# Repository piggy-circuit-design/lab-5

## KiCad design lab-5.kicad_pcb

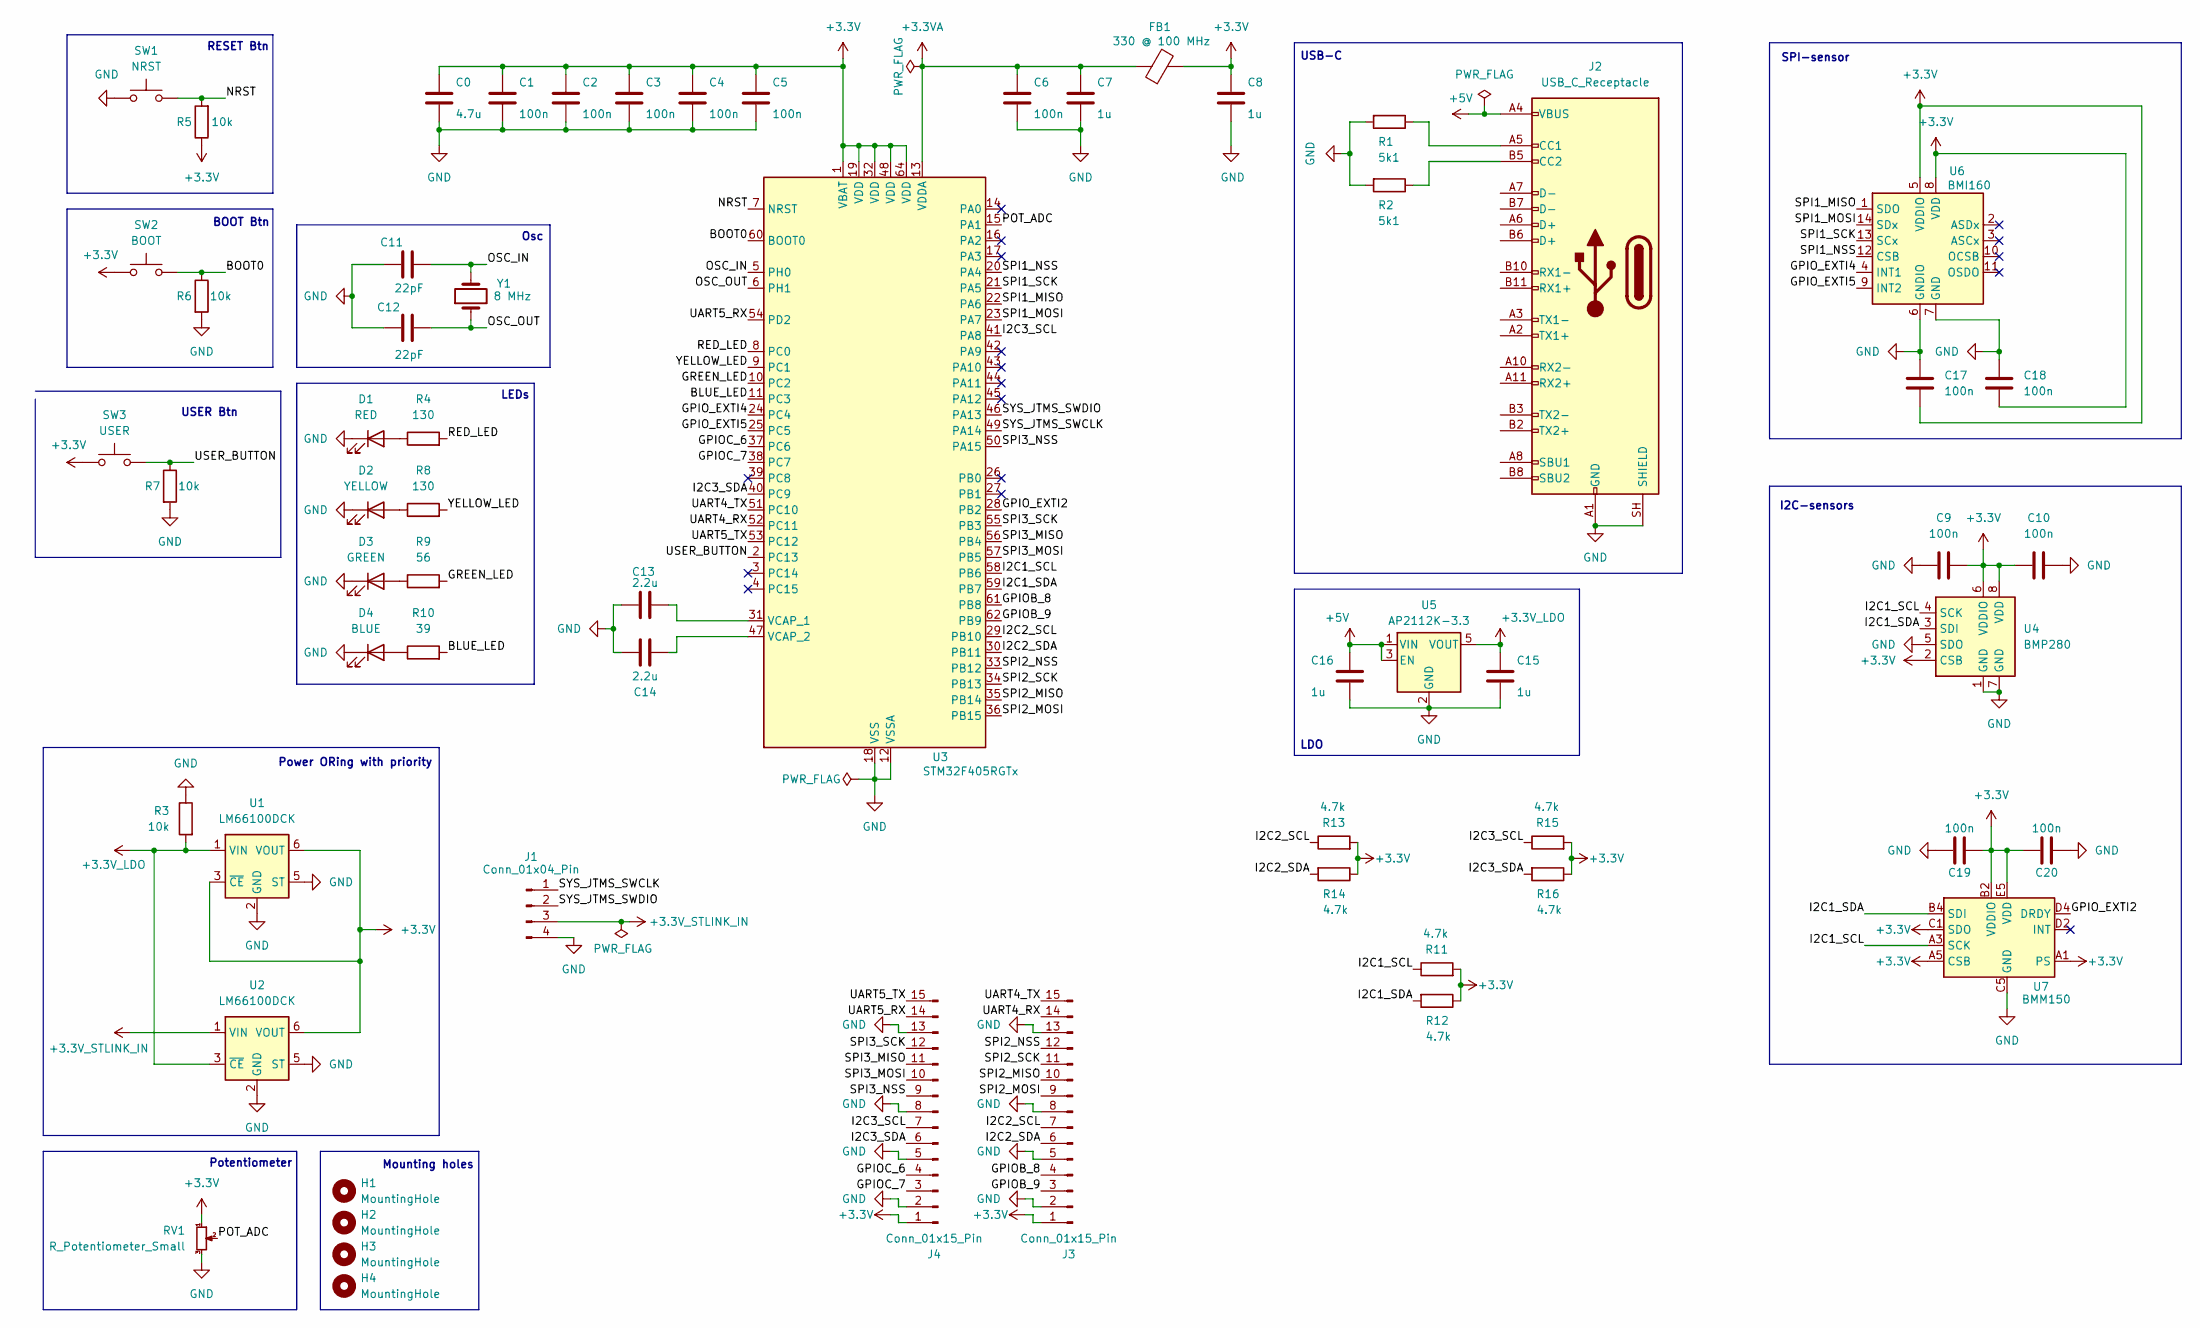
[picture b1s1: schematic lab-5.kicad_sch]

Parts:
C0: 4.7u; C_0603_1608Metric
C1, C2, C3, C4, C5, C6, C9, C10, C17, C18, C19, C20: 100n; C_0402_1005Metric
C7, C8, C15, C16: 1u; C_0603_1608Metric
C11, C12: 22pF; C_0402_1005Metric
C13, C14: 2.2u; C_0402_1005Metric
D1: RED; LED_0805_2012Metric
D2: YELLOW; LED_0805_2012Metric
D3: GREEN; LED_0805_2012Metric
D4: BLUE; LED_0805_2012Metric
FB1: 330 @ 100 MHz; L_0603_1608Metric
H1, H2, H3, H4: MountingHole; MountingHole_2.2mm_M2_Pad
J1: Conn_01x04_Pin; PinHeader_1x04_P2.54mm_Vertical
J2: USB_C_Receptacle; USB_C_Receptacle_Amphenol_12401610E4-2A
J3, J4: Conn_01x15_Pin; PinHeader_1x15_P2.54mm_Vertical
R1, R2: 5k1; R_0603_1608Metric
R3, R5, R6, R7: 10k; R_0402_1005Metric
R4, R8: 130; R_0402_1005Metric
R9: 56; R_0402_1005Metric
R10: 39; R_0402_1005Metric
R11, R12, R13, R14, R15, R16: 4.7k; R_0402_1005Metric
RV1: R_Potentiometer_Small; Potentiometer_Bourns_3224G_Horizontal
SW1: NRST; SW_SPST_PTS647_Sx38
SW2: BOOT; SW_SPST_PTS647_Sx38
SW3: USER; SW_SPST_PTS647_Sx38
U1, U2: LM66100DCK; SOT-363_SC-70-6
U3: STM32F405RGTx; LQFP-64_10x10mm_P0.5mm
U4: BMP280; Bosch_LGA-8_2x2.5mm_P0.65mm_ClockwisePinNumbering
U5: AP2112K-3.3; SOT-23-5
U6: BMI160; Bosch_LGA-14_3x2.5mm_P0.5mm
U7: BMM150; WLCSP-12_1.56x1.56mm_P0.4mm
Y1: 8 MHz; Crystal_SMD_2520-4Pin_2.5x2.0mm

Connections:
+3.3V: C0.1, C1.1, C2.1, C3.1, C4.1, C5.1, C8.1, C9.2, C10.1, C17.1, C18.1, C19.2, C20.1, FB1.2, J3.1, J4.1, R5.1, R11.2, R12.1, R13.2, R14.1, R15.2, R16.1, RV1.1, SW2.2, SW3.2, U1.3 (~CE), U1.6 (VOUT), U2.6 (VOUT), U3.1 (VBAT), U3.19 (VDD), U3.32 (VDD), U3.48 (VDD), U3.64 (VDD), U4.2 (CSB), U4.6 (VDDIO), U4.8 (VDD), U6.5 (VDDIO), U6.8 (VDD), U7.A1 (PS), U7.A5 (CSB), U7.B2 (VDDIO), U7.C1 (SDO), U7.E5 (VDD)
+3.3VA: C6.1, C7.1, FB1.1, U3.13 (VDDA)
+3.3V_LDO: C15.1, R3.2, U1.1 (VIN), U2.3 (~CE), U5.5 (VOUT)
+3.3V_STLINK_IN: J1.3, U2.1 (VIN)
+5V: C16.2, J2.A4 (VBUS), J2.A9 (VBUS), J2.B4 (VBUS), J2.B9 (VBUS), U5.1 (VIN), U5.3 (EN)
/BLUE_LED: R10.2, U3.11 (PC3)
/BOOT0: R6.1, SW2.1, U3.60 (BOOT0)
/GPIOB_8: J3.4, U3.61 (PB8)
/GPIOB_9: J3.3, U3.62 (PB9)
/GPIOC_6: J4.4, U3.37 (PC6)
/GPIOC_7: J4.3, U3.38 (PC7)
/GPIO_EXTI2: U3.28 (PB2), U7.D4 (DRDY)
/GPIO_EXTI4: U3.24 (PC4), U6.4 (INT1)
/GPIO_EXTI5: U3.25 (PC5), U6.9 (INT2)
/GREEN_LED: R9.2, U3.10 (PC2)
/I2C1_SCL: R11.1, U3.58 (PB6), U4.4 (SCK), U7.A3 (SCK)
/I2C1_SDA: R12.2, U3.59 (PB7), U4.3 (SDI), U7.B4 (SDI)
/I2C2_SCL: J3.7, R13.1, U3.29 (PB10)
/I2C2_SDA: J3.6, R14.2, U3.30 (PB11)
/I2C3_SCL: J4.7, R15.1, U3.41 (PA8)
/I2C3_SDA: J4.6, R16.2, U3.40 (PC9)
/NRST: R5.2, SW1.1, U3.7 (NRST)
/OSC_IN: C11.2, U3.5 (PH0), Y1.2
/OSC_OUT: C12.2, U3.6 (PH1), Y1.1
/POT_ADC: RV1.2, U3.15 (PA1)
/RED_LED: R4.2, U3.8 (PC0)
/SPI1_MISO: U3.22 (PA6), U6.1 (SDO)
/SPI1_MOSI: U3.23 (PA7), U6.14 (SDx)
/SPI1_NSS: U3.20 (PA4), U6.12 (CSB)
/SPI1_SCK: U3.21 (PA5), U6.13 (SCx)
/SPI2_MISO: J3.10, U3.35 (PB14)
/SPI2_MOSI: J3.9, U3.36 (PB15)
/SPI2_NSS: J3.12, U3.33 (PB12)
/SPI2_SCK: J3.11, U3.34 (PB13)
/SPI3_MISO: J4.11, U3.56 (PB4)
/SPI3_MOSI: J4.10, U3.57 (PB5)
/SPI3_NSS: J4.9, U3.50 (PA15)
/SPI3_SCK: J4.12, U3.55 (PB3)
/SYS_JTMS_SWCLK: J1.1, U3.49 (PA14)
/SYS_JTMS_SWDIO: J1.2, U3.46 (PA13)
/UART4_RX: J3.14, U3.52 (PC11)
/UART4_TX: J3.15, U3.51 (PC10)
/UART5_RX: J4.14, U3.54 (PD2)
/UART5_TX: J4.15, U3.53 (PC12)
/USER_BUTTON: R7.1, SW3.1, U3.2 (PC13)
/YELLOW_LED: R8.2, U3.9 (PC1)
GND: C0.2, C1.2, C2.2, C3.2, C4.2, C5.2, C6.2, C7.2, C8.2, C9.1, C10.2, C11.1, C12.1, C13.1, C14.2, C15.2, C16.1, C17.2, C18.2, C19.1, C20.2, D1.1 (K), D2.1 (K), D3.1 (K), D4.1 (K), J1.4, J2.A1 (GND), J2.A12 (GND), J2.B1 (GND), J2.B12 (GND), J2.SH (SHIELD), J3.2, J3.5, J3.8, J3.13, J4.2, J4.5, J4.8, J4.13, R1.2, R2.2, R3.1, R6.2, R7.2, RV1.3, SW1.2, U1.2 (GND), U1.5 (ST), U2.2 (GND), U2.5 (ST), U3.12 (VSSA), U3.18 (VSS), U3.63 (VSS), U4.1 (GND), U4.5 (SDO), U4.7 (GND), U5.2 (GND), U6.6 (GNDIO), U6.7 (GND), U7.C5 (GND), U7.E1 (GND), U7.E3 (GND)
unnamed: D1.2 (A), R4.1
unnamed: D2.2 (A), R8.1
unnamed: D3.2 (A), R9.1
unnamed: D4.2 (A), R10.1
unnamed: J2.A5 (CC1), R1.1
unnamed: J2.B5 (CC2), R2.1
unnamed: C13.2, U3.31 (VCAP_1)
unnamed: C14.1, U3.47 (VCAP_2)

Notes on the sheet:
LEDs
SPI-sensor
BOOT Btn
I2C-sensors
Osc
USB-C
Power ORing with priority
LDO
Mounting holes
Potentiometer
RESET Btn
USER Btn

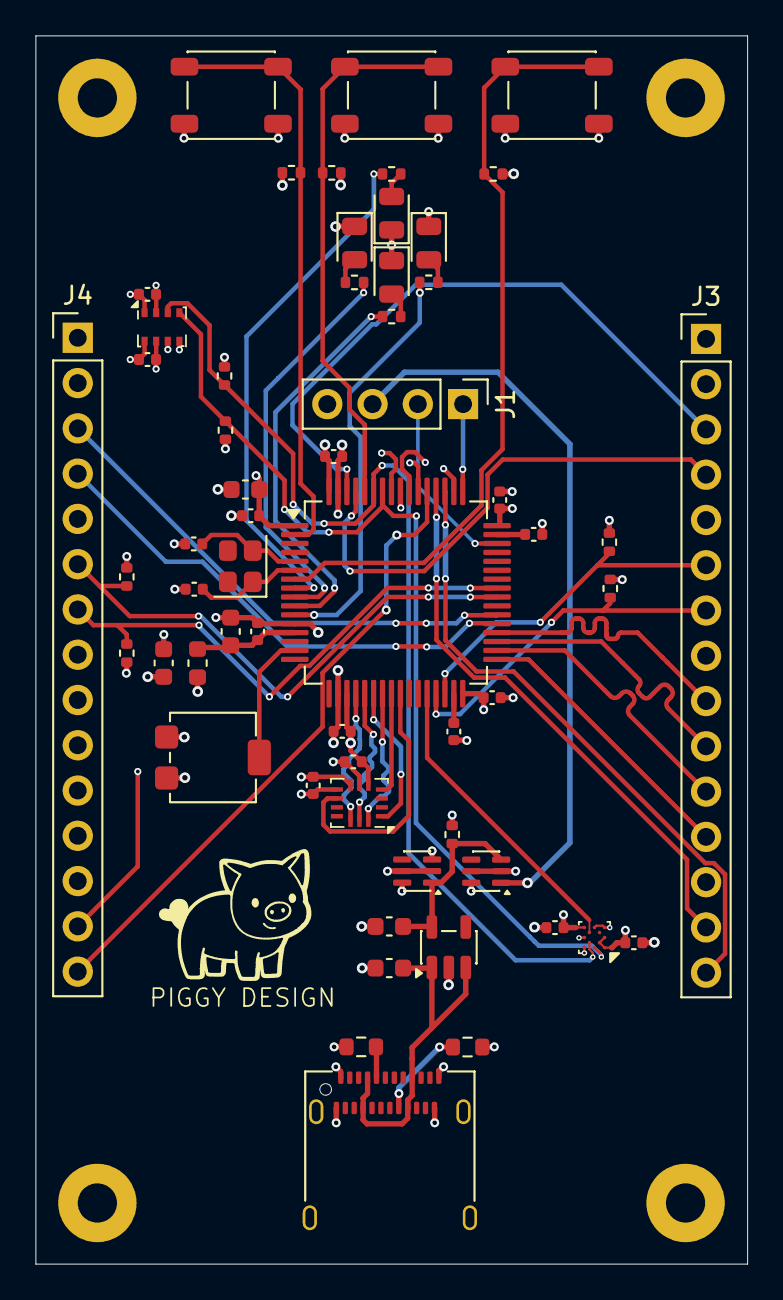
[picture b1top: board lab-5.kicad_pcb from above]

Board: 4 copper layers, 39.9 x 68.9 mm, 62 parts (0 on the bottom side), 55 nets.

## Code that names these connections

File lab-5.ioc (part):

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Mcu.Name=STM32F405RGTx
Mcu.Package=LQFP64
Mcu.UserName=STM32F405RGTx
PA1.GPIOParameters=GPIO_Label
PA1.GPIO_Label=POT_ADC
PA1.Signal=ADCx_IN1
PA13.Mode=Serial_Wire
PA13.Signal=SYS_JTMS-SWDIO
PA14.Mode=Serial_Wire
PA14.Signal=SYS_JTCK-SWCLK
PA15.Mode=NSS_Signal_Hard_Output
PA15.Signal=SPI3_NSS
PA4.Mode=NSS_Signal_Hard_Output
PA4.Signal=SPI1_NSS
PA5.Mode=Full_Duplex_Master
PA5.Signal=SPI1_SCK
PA6.Mode=Full_Duplex_Master
PA6.Signal=SPI1_MISO
PA7.Mode=Full_Duplex_Master
PA7.Signal=SPI1_MOSI
PA8.Mode=I2C
PA8.Signal=I2C3_SCL
PB10.Mode=I2C
PB10.Signal=I2C2_SCL
PB11.Mode=I2C
PB11.Signal=I2C2_SDA
PB12.Mode=NSS_Signal_Hard_Output
PB12.Signal=SPI2_NSS
PB13.Mode=Full_Duplex_Master
PB13.Signal=SPI2_SCK
PB14.Mode=Full_Duplex_Master
PB14.Signal=SPI2_MISO
PB15.Mode=Full_Duplex_Master
PB15.Signal=SPI2_MOSI
PB2.Signal=GPXTI2
PB3.Mode=Full_Duplex_Master
PB3.Signal=SPI3_SCK
PB4.Mode=Full_Duplex_Master
PB4.Signal=SPI3_MISO
PB5.Mode=Full_Duplex_Master
PB5.Signal=SPI3_MOSI
PB6.Mode=I2C
PB6.Signal=I2C1_SCL
PB7.Mode=I2C
PB7.Signal=I2C1_SDA
PC0.GPIOParameters=GPIO_Label
PC0.GPIO_Label=RED_LED
PC0.Signal=GPIO_Output
PC1.GPIOParameters=GPIO_Label
PC1.GPIO_Label=YELLOW_LED
PC1.Signal=GPIO_Output
PC10.Mode=Asynchronous
PC10.Signal=UART4_TX
PC11.Mode=Asynchronous
PC11.Signal=UART4_RX
PC12.Mode=Asynchronous
PC12.Signal=UART5_TX
PC13-ANTI_TAMP.GPIOParameters=GPIO_Label
PC13-ANTI_TAMP.GPIO_Label=USER_BUTTON
PC13-ANTI_TAMP.Signal=GPIO_Input
PC2.GPIOParameters=GPIO_Label
PC2.GPIO_Label=GREEN_LED
PC2.Signal=GPIO_Output
PC3.GPIOParameters=GPIO_Label
PC3.GPIO_Label=BLUE_LED
PC3.Signal=GPIO_Output
PC4.Signal=GPXTI4
PC5.Signal=GPXTI5
PC9.Mode=I2C
PC9.Signal=I2C3_SDA
PD2.Mode=Asynchronous
PD2.Signal=UART5_RX
PH0-OSC_IN.Mode=HSE-External-Oscillator
PH0-OSC_IN.Signal=RCC_OSC_IN
PH1-OSC_OUT.Mode=HSE-External-Oscillator
PH1-OSC_OUT.Signal=RCC_OSC_OUT
RCC.HSE_VALUE=25000000
RCC.SYSCLKFreq_VALUE=16000000
board=custom

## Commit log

2026-05-13 add BMP280 via I2C
2026-05-13 added the BMI160 and logo, full board refactoring
2026-05-17 Added bmm150 and connected all other interfaces
2026-05-17 refactoring
2026-05-17 changed spi1 tracks lengh
2026-05-17 last
